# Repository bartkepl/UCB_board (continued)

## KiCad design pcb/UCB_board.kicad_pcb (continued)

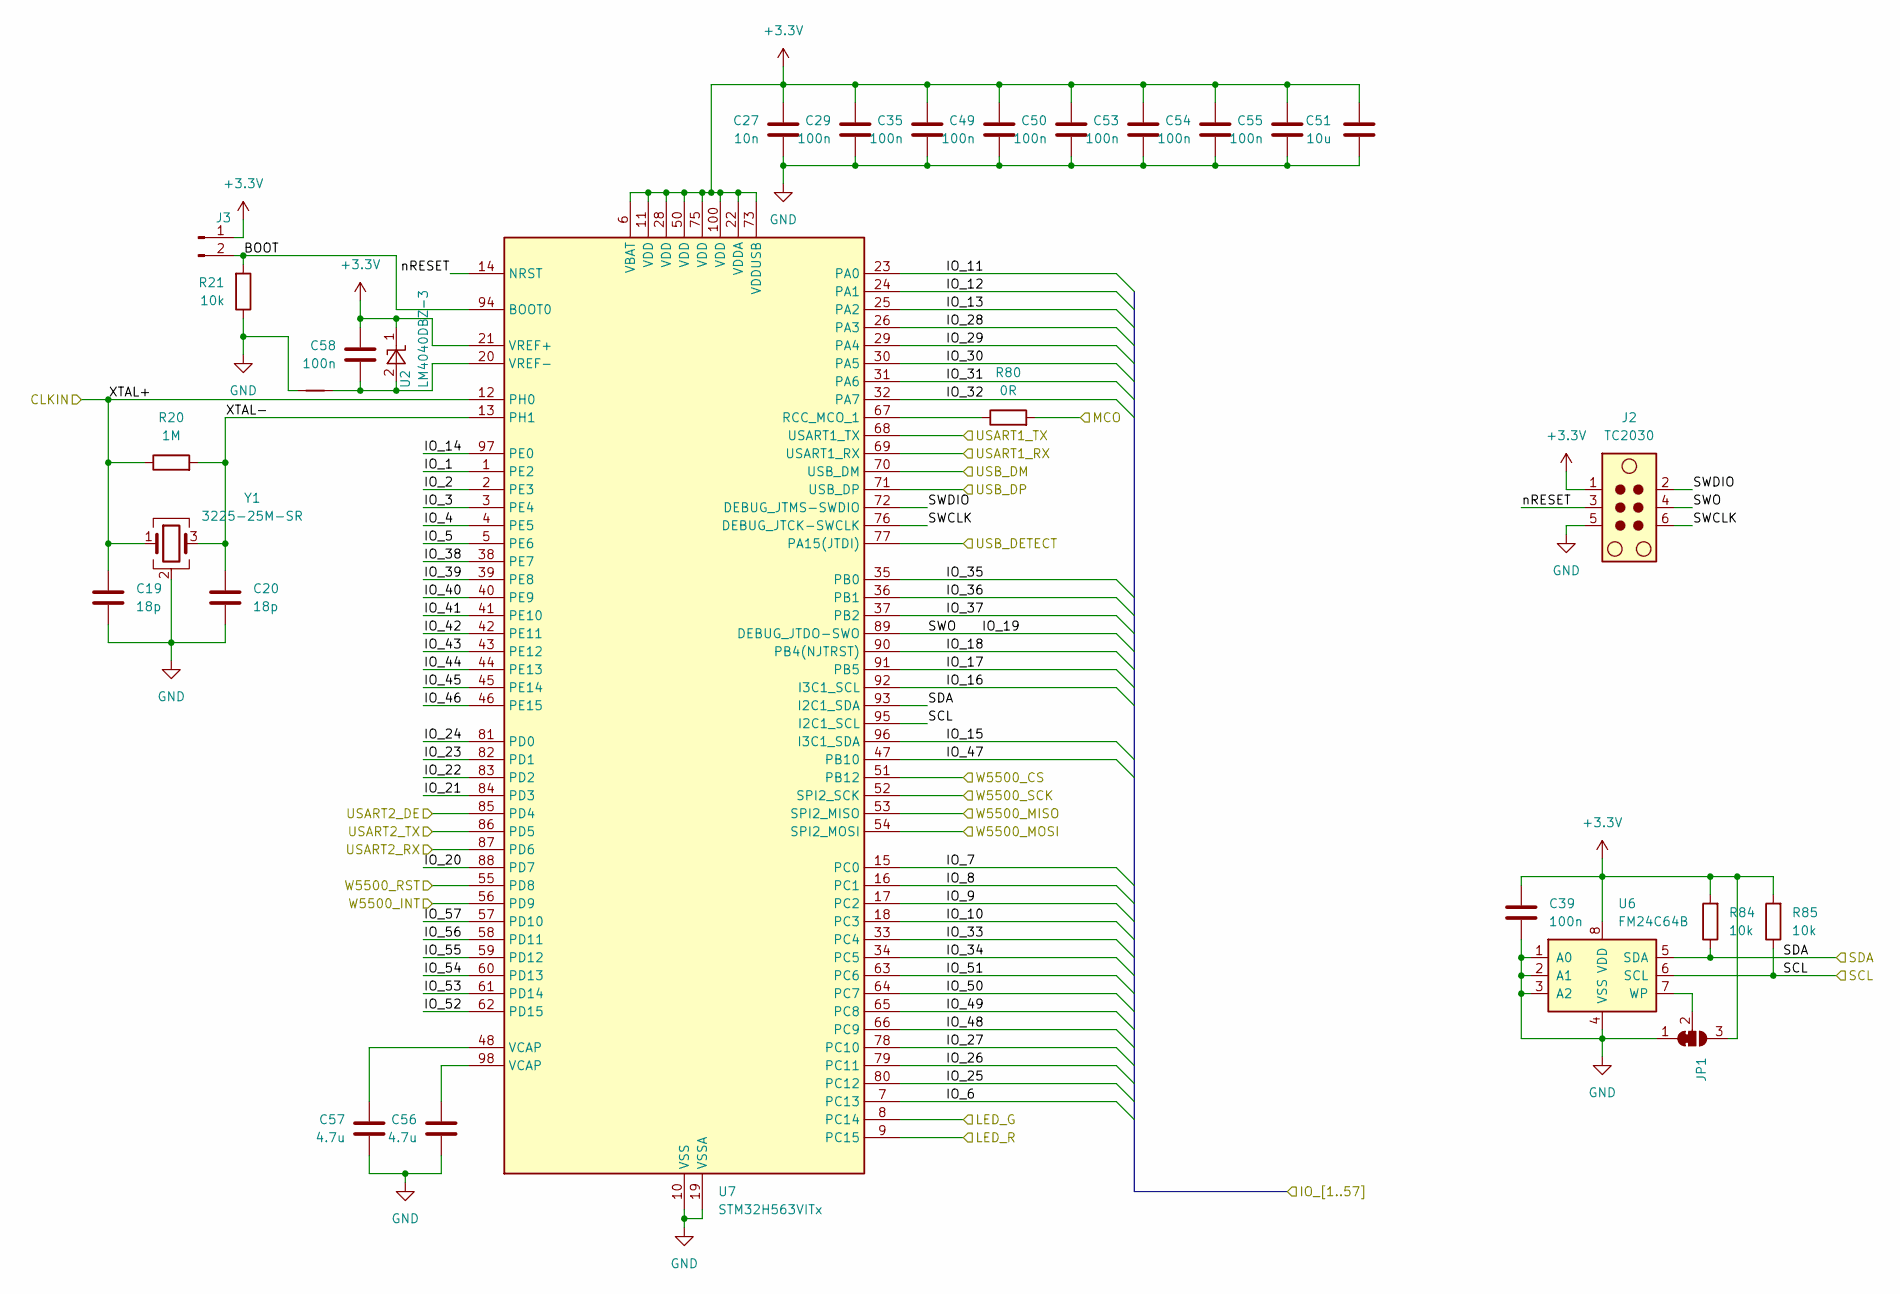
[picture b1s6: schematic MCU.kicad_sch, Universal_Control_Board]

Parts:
C19, C20: 18p; C_0402_1005Metric_Pad0.74x0.62mm_HandSolder
C27: 10n; C_0603_1608Metric; Manufacturer_Part_Number GRM1885C1H103JA01J
C29, C35, C39, C49, C50, C53, C54, C55, C58: 100n; C_0603_1608Metric; Manufacturer_Part_Number GRM188R71H104KA93D
C51: 10u; C_1206_3216Metric; Manufacturer_Part_Number CL31B106KBHNNNE
C56, C57: 4.7u; C_0603_1608Metric; Manufacturer_Part_Number 0603X475K100CT
J2: TC2030; Tag-Connect_TC2030-IDC-NL_2x03_P1.27mm_Vertical
J3: Conn_01x02_Pin; PinHeader_1x02_P2.00mm_Vertical
JP1: SolderJumper_3_Bridged12; SolderJumper-3_P1.3mm_Bridged12_Pad1.0x1.5mm
NT1: NetTie_2; NetTie-2_SMD_Pad0.5mm
R20: 1M; R_0603_1608Metric; Manufacturer_Part_Number 0603SAF1004T5E
R21, R84, R85: 10k; R_0603_1608Metric; Manufacturer_Part_Number CRCW060310K0FKTABC
R80: 0R; R_0402_1005Metric; Manufacturer_Part_Number CRCW04020000Z0TDBC
U2: LM4040DBZ-3; SOT-23_Handsoldering; Manufacturer_Part_Number LM4040DBZ-3
U6: FM24C64B; SOIC-8_3.9x4.9mm_P1.27mm; Manufacturer_Part_Number FM24C64B
U7: STM32H563VITx; LQFP-100_14x14mm_P0.5mm; Manufacturer_Part_Number STM32H563VIT6
Y1: 3225-25M-SR; Crystal_SMD_3225-4Pin_3.2x2.5mm

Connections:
+3.3V: C27.2, C29.2, C35.2, C39.1, C49.2, C50.2, C51.1, C53.2, C54.2, C55.2, C58.2, J2.1, J3.1, JP1.3 (B), R84.2, R85.2, U2.1 (K), U6.8 (VDD), U7.6 (VBAT), U7.11 (VDD), U7.21 (VREF+), U7.22 (VDDA), U7.28 (VDD), U7.50 (VDD), U7.73 (VDDUSB), U7.75 (VDD), U7.100 (VDD); also elsewhere on the board
/ConnectorDIN41612/DE: U7.85 (PD4); also elsewhere on the board
/ConnectorDIN41612/RxD: U7.87 (PD6); also elsewhere on the board
/ConnectorDIN41612/TxD: U7.86 (PD5); also elsewhere on the board
/ConnectorDIN41612/USART+: U7.68 (USART1_TX); also elsewhere on the board
/ConnectorDIN41612/USART-: U7.69 (USART1_RX); also elsewhere on the board
/ConnectorDIN41612/USB_D+: U7.71 (USB_DP); also elsewhere on the board
/ConnectorDIN41612/USB_D-: U7.70 (USB_DM); also elsewhere on the board
/ConnectorDIN41612/USB_DET: U7.77 (PA15(JTDI)); also elsewhere on the board
/EthernetPHY/CS: U7.51 (PB12); also elsewhere on the board
/EthernetPHY/INT: U7.56 (PD9); also elsewhere on the board
/EthernetPHY/MISO: U7.53 (SPI2_MISO); also elsewhere on the board
/EthernetPHY/MOSI: U7.54 (SPI2_MOSI); also elsewhere on the board
/EthernetPHY/RST: U7.55 (PD8); also elsewhere on the board
/EthernetPHY/SCK: U7.52 (SPI2_SCK); also elsewhere on the board
/EthernetPHY/XO+: R80.2; also elsewhere on the board
/MCU/BOOT: J3.2, R21.2, U7.94 (BOOT0)
/MCU/IO_1: U7.1 (PE2); also elsewhere on the board
/MCU/IO_2: U7.2 (PE3); also elsewhere on the board
/MCU/IO_3: U7.3 (PE4); also elsewhere on the board
/MCU/IO_4: U7.4 (PE5); also elsewhere on the board
/MCU/IO_5: U7.5 (PE6); also elsewhere on the board
/MCU/IO_6: U7.7 (PC13); also elsewhere on the board
/MCU/IO_7: U7.15 (PC0); also elsewhere on the board
/MCU/IO_8: U7.16 (PC1); also elsewhere on the board
/MCU/IO_9: U7.17 (PC2); also elsewhere on the board
/MCU/IO_10: U7.18 (PC3); also elsewhere on the board
/MCU/IO_11: U7.23 (PA0); also elsewhere on the board
/MCU/IO_12: U7.24 (PA1); also elsewhere on the board
/MCU/IO_13: U7.25 (PA2); also elsewhere on the board
/MCU/IO_14: U7.97 (PE0); also elsewhere on the board
/MCU/IO_15: U7.96 (I3C1_SDA); also elsewhere on the board
/MCU/IO_16: U7.92 (I3C1_SCL); also elsewhere on the board
/MCU/IO_17: U7.91 (PB5); also elsewhere on the board
/MCU/IO_18: U7.90 (PB4(NJTRST)); also elsewhere on the board
/MCU/IO_19: J2.4, U7.89 (DEBUG_JTDO-SWO); also elsewhere on the board
/MCU/IO_20: U7.88 (PD7); also elsewhere on the board
/MCU/IO_21: U7.84 (PD3); also elsewhere on the board
/MCU/IO_22: U7.83 (PD2); also elsewhere on the board
/MCU/IO_23: U7.82 (PD1); also elsewhere on the board
/MCU/IO_24: U7.81 (PD0); also elsewhere on the board
/MCU/IO_25: U7.80 (PC12); also elsewhere on the board
/MCU/IO_26: U7.79 (PC11); also elsewhere on the board
/MCU/IO_27: U7.78 (PC10); also elsewhere on the board
/MCU/IO_28: U7.26 (PA3); also elsewhere on the board
/MCU/IO_29: U7.29 (PA4); also elsewhere on the board
/MCU/IO_30: U7.30 (PA5); also elsewhere on the board
/MCU/IO_31: U7.31 (PA6); also elsewhere on the board
/MCU/IO_32: U7.32 (PA7); also elsewhere on the board
/MCU/IO_33: U7.33 (PC4); also elsewhere on the board
/MCU/IO_34: U7.34 (PC5); also elsewhere on the board
/MCU/IO_35: U7.35 (PB0); also elsewhere on the board
/MCU/IO_36: U7.36 (PB1); also elsewhere on the board
/MCU/IO_37: U7.37 (PB2); also elsewhere on the board
/MCU/IO_38: U7.38 (PE7); also elsewhere on the board
/MCU/IO_39: U7.39 (PE8); also elsewhere on the board
/MCU/IO_40: U7.40 (PE9); also elsewhere on the board
/MCU/IO_41: U7.41 (PE10); also elsewhere on the board
/MCU/IO_42: U7.42 (PE11); also elsewhere on the board
/MCU/IO_43: U7.43 (PE12); also elsewhere on the board
/MCU/IO_44: U7.44 (PE13); also elsewhere on the board
/MCU/IO_45: U7.45 (PE14); also elsewhere on the board
/MCU/IO_46: U7.46 (PE15); also elsewhere on the board
/MCU/IO_47: U7.47 (PB10); also elsewhere on the board
/MCU/IO_48: U7.66 (PC9); also elsewhere on the board
/MCU/IO_49: U7.65 (PC8); also elsewhere on the board
/MCU/IO_50: U7.64 (PC7); also elsewhere on the board
/MCU/IO_51: U7.63 (PC6); also elsewhere on the board
/MCU/IO_52: U7.62 (PD15); also elsewhere on the board
/MCU/IO_53: U7.61 (PD14); also elsewhere on the board
/MCU/IO_54: U7.60 (PD13); also elsewhere on the board
/MCU/IO_55: U7.59 (PD12); also elsewhere on the board
/MCU/IO_56: U7.58 (PD11); also elsewhere on the board
/MCU/IO_57: U7.57 (PD10); also elsewhere on the board
/MCU/LED_G: U7.8 (PC14); also elsewhere on the board
/MCU/LED_R: U7.9 (PC15); also elsewhere on the board
/MCU/SCL: R85.1, U6.6 (SCL), U7.95 (I2C1_SCL); also elsewhere on the board
/MCU/SDA: R84.1, U6.5 (SDA), U7.93 (I2C1_SDA); also elsewhere on the board
/MCU/SWCLK: J2.6, U7.76 (DEBUG_JTCK-SWCLK)
/MCU/SWDIO: J2.2, U7.72 (DEBUG_JTMS-SWDIO)
/MCU/XTAL+: C19.1, R20.1, U7.12 (PH0), Y1.1; also elsewhere on the board
/MCU/XTAL-: C20.1, R20.2, U7.13 (PH1), Y1.3
/MCU/nRESET: J2.3, U7.14 (NRST)
GND: C19.2, C20.2, C27.1, C29.1, C35.1, C39.2, C49.1, C50.1, C51.2, C53.1, C54.1, C55.1, C56.1, C57.1, J2.5, JP1.1 (A), NT1.1, R21.1, U6.1 (A0), U6.2 (A1), U6.3 (A2), U6.4 (VSS), U7.10 (VSS), U7.19 (VSSA), U7.27 (VSS), U7.49 (VSS), U7.74 (VSS), U7.99 (VSS), Y1.2 (G), Y1.4 (G); also elsewhere on the board
unnamed: C56.2, U7.98 (VCAP)
unnamed: C57.2, U7.48 (VCAP)
unnamed: JP1.2 (C), U6.7 (WP)
unnamed: C58.1, NT1.2, U2.2 (A), U7.20 (VREF-)
unnamed: R80.1, U7.67 (RCC_MCO_1)

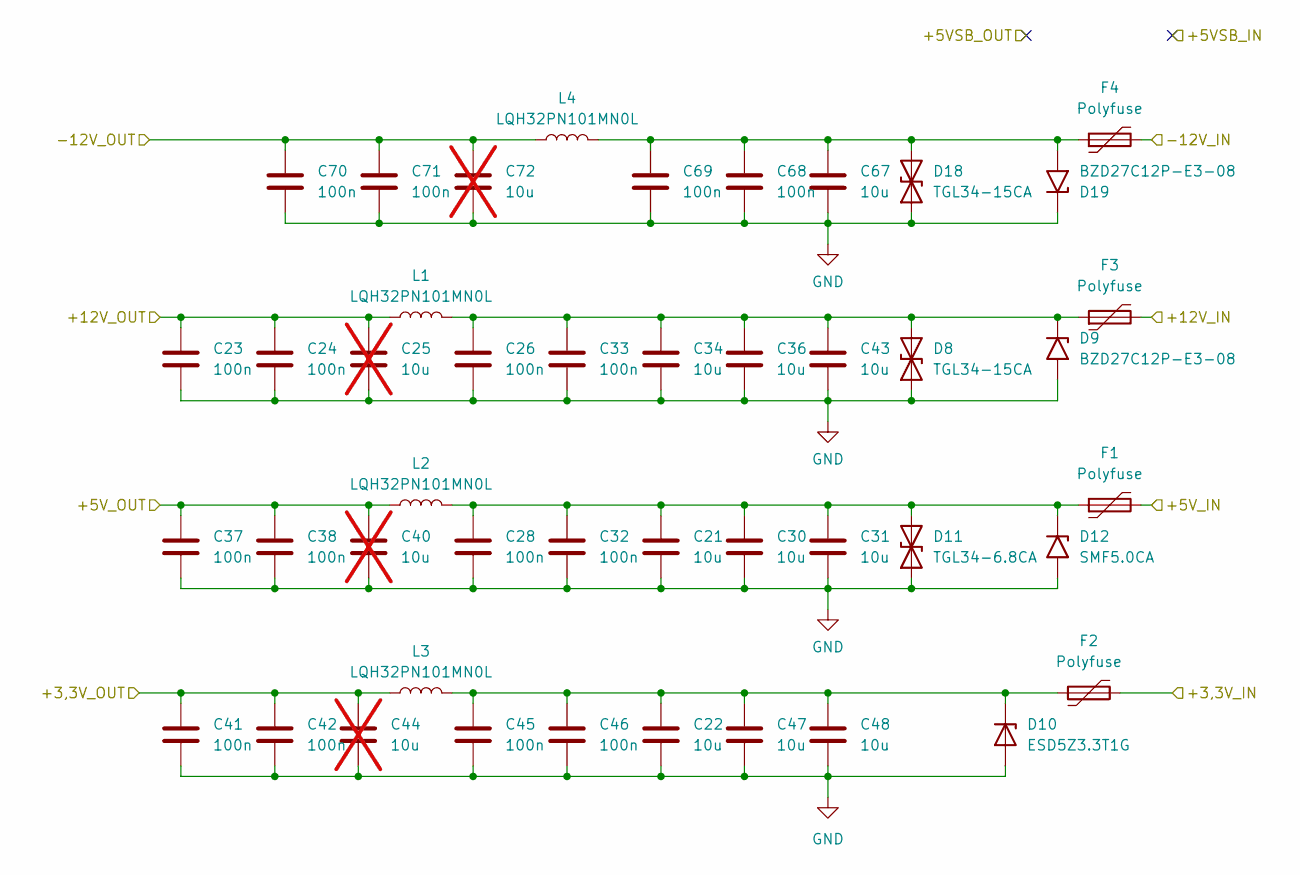
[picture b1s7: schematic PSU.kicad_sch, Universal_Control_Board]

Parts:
C21, C22, C30, C31, C34, C36, C43, C47, C48, C67: 10u; C_1206_3216Metric; Manufacturer_Part_Number CL31B106KBHNNNE
C23, C24, C26, C28, C32, C33, C37, C38, C41, C42, C45, C46, C68, C69, C70, C71: 100n; C_0603_1608Metric; Manufacturer_Part_Number GRM188R71H104KA93D
C25, C40, C44, C72: 10u; C_1206_3216Metric_Pad1.33x1.80mm_HandSolder; not fitted
D8, D18: TGL34-15CA; D_MiniMELF; Manufacturer_Part_Number TGL34-15CA
D9, D19: BZD27C12P-E3-08; D_SMF; Manufacturer_Part_Number BZD27C12P-E3-08
D10: ESD5Z3.3T1G; D_SOD-523; Manufacturer_Part_Number ESD5Z3.3T1G
D11: TGL34-6.8CA; D_MiniMELF; Manufacturer_Part_Number TGL34-6.8CA
D12: SMF5.0CA; D_SMF; Manufacturer_Part_Number SMF5.0CA
F1, F2, F3, F4: Polyfuse; Fuse_1206_3216Metric_Pad1.42x1.75mm_HandSolder; Manufacturer_Part_Number SN020-30
L1, L2, L3, L4: LQH32PN101MN0L; L_1210_3225Metric; Manufacturer_Part_Number LQH32PN101MN0L

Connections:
+3.3V: C41.1, C42.1, C44.1, L3.1; also elsewhere on the board
+5V: C37.1, C38.1, C40.1, L2.1; also elsewhere on the board
+12V: C23.1, C24.1, C25.1, L1.1; also elsewhere on the board
-12V: C70.1, C71.1, C72.1, L4.1; also elsewhere on the board
/ConnectorDIN41612/PSU/+3,3V_IN: F2.2; also elsewhere on the board
/ConnectorDIN41612/PSU/+5V_IN: F1.2; also elsewhere on the board
/ConnectorDIN41612/PSU/+12V_IN: F3.2; also elsewhere on the board
/ConnectorDIN41612/PSU/-12V_IN: F4.2; also elsewhere on the board
GND: C21.2, C22.2, C23.2, C24.2, C25.2, C26.2, C28.2, C30.2, C31.2, C32.2, C33.2, C34.2, C36.2, C37.2, C38.2, C40.2, C41.2, C42.2, C43.2, C44.2, C45.2, C46.2, C47.2, C48.2, C67.2, C68.2, C69.2, C70.2, C71.2, C72.2, D8.1 (A1), D9.2 (A2), D10.2 (A), D11.1 (A1), D12.2 (A2), D18.1 (A1), D19.1 (A1); also elsewhere on the board
unnamed: C26.1, C33.1, C34.1, C36.1, C43.1, D8.2 (A2), D9.1 (A1), F3.1, L1.2
unnamed: C22.1, C45.1, C46.1, C47.1, C48.1, D10.1 (K), F2.1, L3.2
unnamed: C21.1, C28.1, C30.1, C31.1, C32.1, D11.2 (A2), D12.1 (A1), F1.1, L2.2
unnamed: C67.1, C68.1, C69.1, D18.2 (A2), D19.2 (A2), F4.1, L4.2

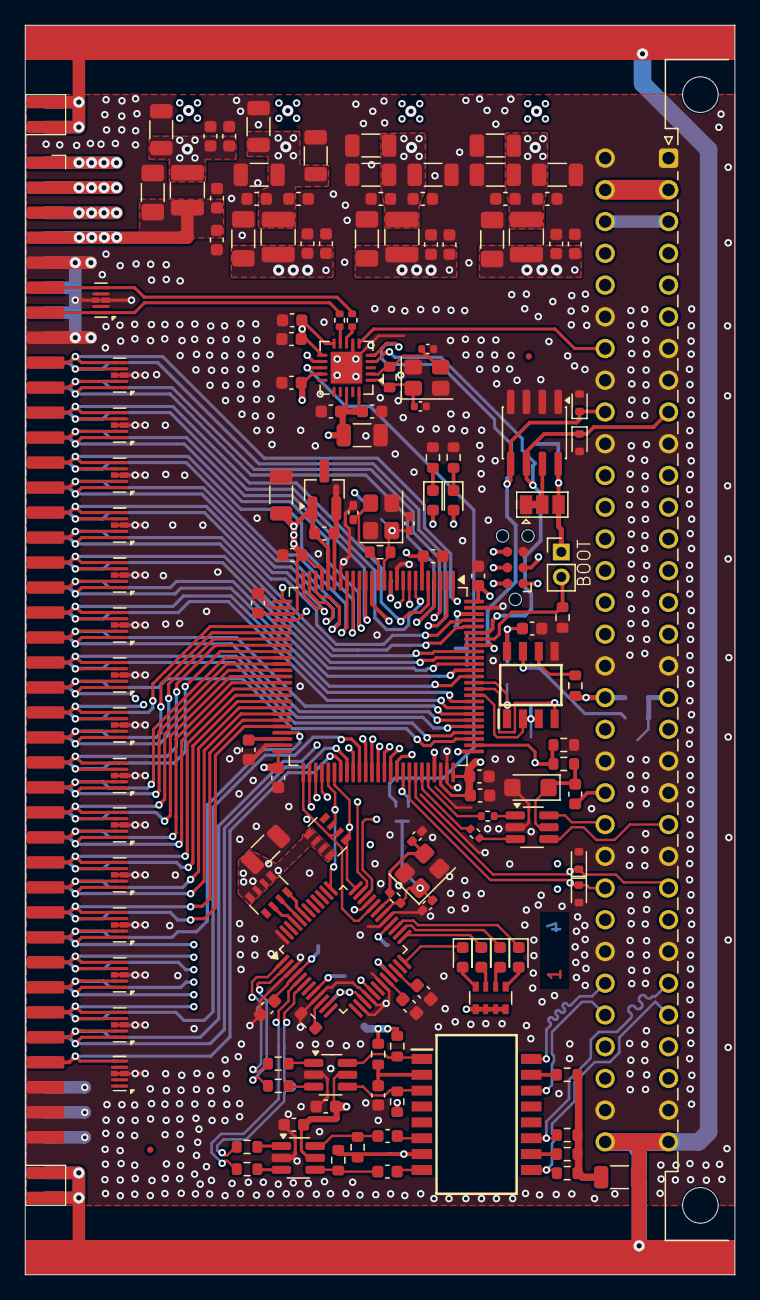
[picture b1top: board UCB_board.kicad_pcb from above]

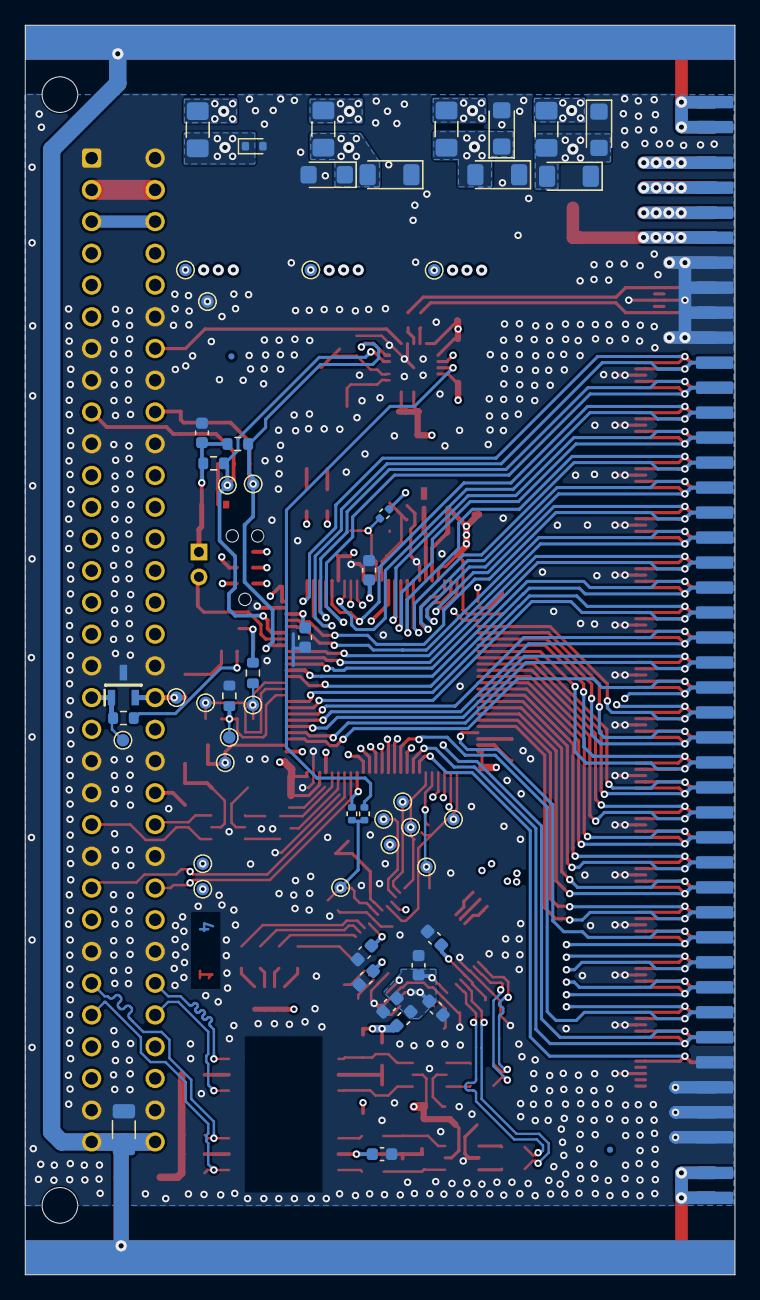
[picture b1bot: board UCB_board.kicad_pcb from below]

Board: 4 copper layers, 56.8 x 100.0 mm, 201 parts (55 on the bottom side), 163 nets.

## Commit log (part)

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2026-03-27 Project files upload
2026-03-30 New power design
2026-03-31 Add connections and new footprints
2026-04-06 Add UniConnector for io expansion (2.0mm pinheader)
2026-04-09 Add junction and bus entries to UniConnector schematic
2026-04-13 UniConnector new traces
2026-04-14 Added SI5351C
2026-04-14 Clock rounting
2026-04-15 New routing
2026-04-15 More routing
2026-04-16 More routing ...
2026-04-17 Added ESD protection to UniConnector, more routing and polishing
2026-04-19 Added vias and cleaned pcb. Board finished
2026-04-19 Prepared for production
2026-04-21 Add ferrite beads; update MCU pinout
    Schematic and PCB updates: add FerriteBead_Small symbol two instances (FB1, FB2) with matching 0603 inductor footprints on the board. Firmware (.ioc) changes: removed I3C config, added TIM2/TIM5/USAR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
2026-05-10 Crystal footprint changed, routing and eth trafo to correct
2026-05-11 Corected mistakes found on RDE_board
